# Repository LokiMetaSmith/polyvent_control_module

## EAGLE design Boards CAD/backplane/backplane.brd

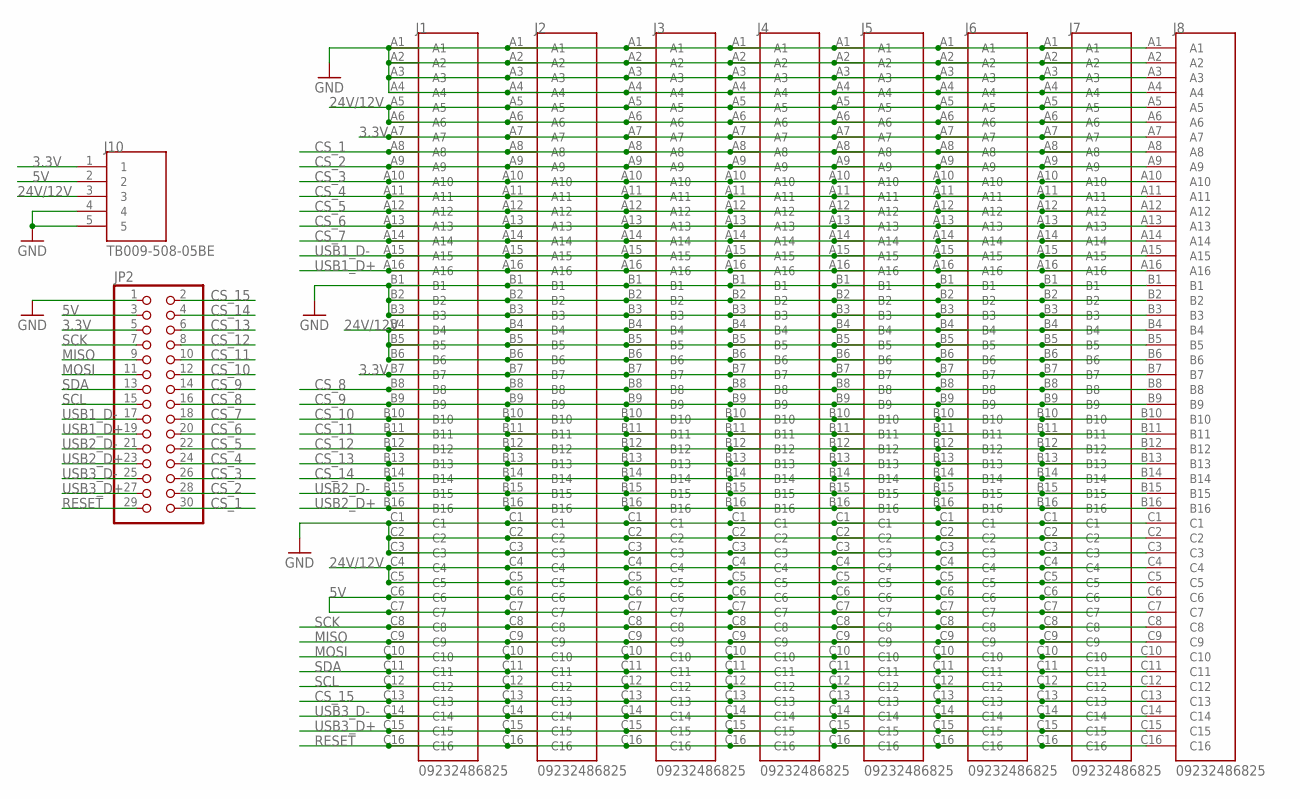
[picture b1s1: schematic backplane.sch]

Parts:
J1, J2, J3, J4, J5, J6, J7, J8: 09232486825; HARTING_09232486825
J10: TB009-508-05BE; CUI_TB009-508-05BE
JP2: PINHD-2X15; 2X15

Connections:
3.3V: J1.A7, J1.B7, J2.A7, J2.B7, J3.A7, J3.B7, J4.A7, J4.B7, J5.A7, J5.B7, J6.A7, J6.B7, J7.A7, J7.B7, J8.A7, J8.B7, J10.1, JP2.5
5V: J1.C6, J1.C7, J2.C6, J2.C7, J3.C6, J3.C7, J4.C6, J4.C7, J5.C6, J5.C7, J6.C6, J6.C7, J7.C6, J7.C7, J8.C6, J8.C7, J10.2, JP2.3
24V/12V: J1.A5, J1.A6, J1.B4, J1.B5, J1.B6, J1.C4, J1.C5, J2.A5, J2.A6, J2.B4, J2.B5, J2.B6, J2.C4, J2.C5, J3.A5, J3.A6, J3.B4, J3.B5, J3.B6, J3.C4, J3.C5, J4.A5, J4.A6, J4.B4, J4.B5, J4.B6, J4.C4, J4.C5, J5.A5, J5.A6, J5.B4, J5.B5, J5.B6, J5.C4, J5.C5, J6.A5, J6.A6, J6.B4, J6.B5, J6.B6, J6.C4, J6.C5, J7.A5, J7.A6, J7.B4, J7.B5, J7.B6, J7.C4, J7.C5, J8.A5, J8.A6, J8.B4, J8.B5, J8.B6, J8.C4, J8.C5, J10.3
CS_1: J1.A8, J2.A8, J3.A8, J4.A8, J5.A8, J6.A8, J7.A8, J8.A8, JP2.30
CS_2: J1.A9, J2.A9, J3.A9, J4.A9, J5.A9, J6.A9, J7.A9, J8.A9, JP2.28
CS_3: J1.A10, J2.A10, J3.A10, J4.A10, J5.A10, J6.A10, J7.A10, J8.A10, JP2.26
CS_4: J1.A11, J2.A11, J3.A11, J4.A11, J5.A11, J6.A11, J7.A11, J8.A11, JP2.24
CS_5: J1.A12, J2.A12, J3.A12, J4.A12, J5.A12, J6.A12, J7.A12, J8.A12, JP2.22
CS_6: J1.A13, J2.A13, J3.A13, J4.A13, J5.A13, J6.A13, J7.A13, J8.A13, JP2.20
CS_7: J1.A14, J2.A14, J3.A14, J4.A14, J5.A14, J6.A14, J7.A14, J8.A14, JP2.18
CS_8: J1.B8, J2.B8, J3.B8, J4.B8, J5.B8, J6.B8, J7.B8, J8.B8, JP2.16
CS_9: J1.B9, J2.B9, J3.B9, J4.B9, J5.B9, J6.B9, J7.B9, J8.B9, JP2.14
CS_10: J1.B10, J2.B10, J3.B10, J4.B10, J5.B10, J6.B10, J7.B10, J8.B10, JP2.12
CS_11: J1.B11, J2.B11, J3.B11, J4.B11, J5.B11, J6.B11, J7.B11, J8.B11, JP2.10
CS_12: J1.B12, J2.B12, J3.B12, J4.B12, J5.B12, J6.B12, J7.B12, J8.B12, JP2.8
CS_13: J1.B13, J2.B13, J3.B13, J4.B13, J5.B13, J6.B13, J7.B13, J8.B13, JP2.6
CS_14: J1.B14, J2.B14, J3.B14, J4.B14, J5.B14, J6.B14, J7.B14, J8.B14, JP2.4
CS_15: J1.C13, J2.C13, J3.C13, J4.C13, J5.C13, J6.C13, J7.C13, J8.C13, JP2.2
GND: J1.A1, J1.A2, J1.A3, J1.A4, J1.B1, J1.B2, J1.B3, J1.C1, J1.C2, J1.C3, J2.A1, J2.A2, J2.A3, J2.A4, J2.B1, J2.B2, J2.B3, J2.C1, J2.C2, J2.C3, J3.A1, J3.A2, J3.A3, J3.A4, J3.B1, J3.B2, J3.B3, J3.C1, J3.C2, J3.C3, J4.A1, J4.A2, J4.A3, J4.A4, J4.B1, J4.B2, J4.B3, J4.C1, J4.C2, J4.C3, J5.A1, J5.A2, J5.A3, J5.A4, J5.B1, J5.B2, J5.B3, J5.C1, J5.C2, J5.C3, J6.A1, J6.A2, J6.A3, J6.A4, J6.B1, J6.B2, J6.B3, J6.C1, J6.C2, J6.C3, J7.A1, J7.A2, J7.A3, J7.A4, J7.B1, J7.B2, J7.B3, J7.C1, J7.C2, J7.C3, J8.A1, J8.A2, J8.A3, J8.A4, J8.B1, J8.B2, J8.B3, J8.C1, J8.C2, J8.C3, J10.4, J10.5, JP2.1
MISO: J1.C9, J2.C9, J3.C9, J4.C9, J5.C9, J6.C9, J7.C9, J8.C9, JP2.9
MOSI: J1.C10, J2.C10, J3.C10, J4.C10, J5.C10, J6.C10, J7.C10, J8.C10, JP2.11
RESET: J1.C16, J2.C16, J3.C16, J4.C16, J5.C16, J6.C16, J7.C16, J8.C16, JP2.29
SCK: J1.C8, J2.C8, J3.C8, J4.C8, J5.C8, J6.C8, J7.C8, J8.C8, JP2.7
SCL: J1.C12, J2.C12, J3.C12, J4.C12, J5.C12, J6.C12, J7.C12, J8.C12, JP2.15
SDA: J1.C11, J2.C11, J3.C11, J4.C11, J5.C11, J6.C11, J7.C11, J8.C11, JP2.13
USB1_D+: J1.A16, J2.A16, J3.A16, J4.A16, J5.A16, J6.A16, J7.A16, J8.A16, JP2.19
USB1_D-: J1.A15, J2.A15, J3.A15, J4.A15, J5.A15, J6.A15, J7.A15, J8.A15, JP2.17
USB2_D+: J1.B16, J2.B16, J3.B16, J4.B16, J5.B16, J6.B16, J7.B16, J8.B16, JP2.23
USB2_D-: J1.B15, J2.B15, J3.B15, J4.B15, J5.B15, J6.B15, J7.B15, J8.B15, JP2.21
USB3_D+: J1.C15, J2.C15, J3.C15, J4.C15, J5.C15, J6.C15, J7.C15, J8.C15, JP2.27
USB3_D-: J1.C14, J2.C14, J3.C14, J4.C14, J5.C14, J6.C14, J7.C14, J8.C14, JP2.25

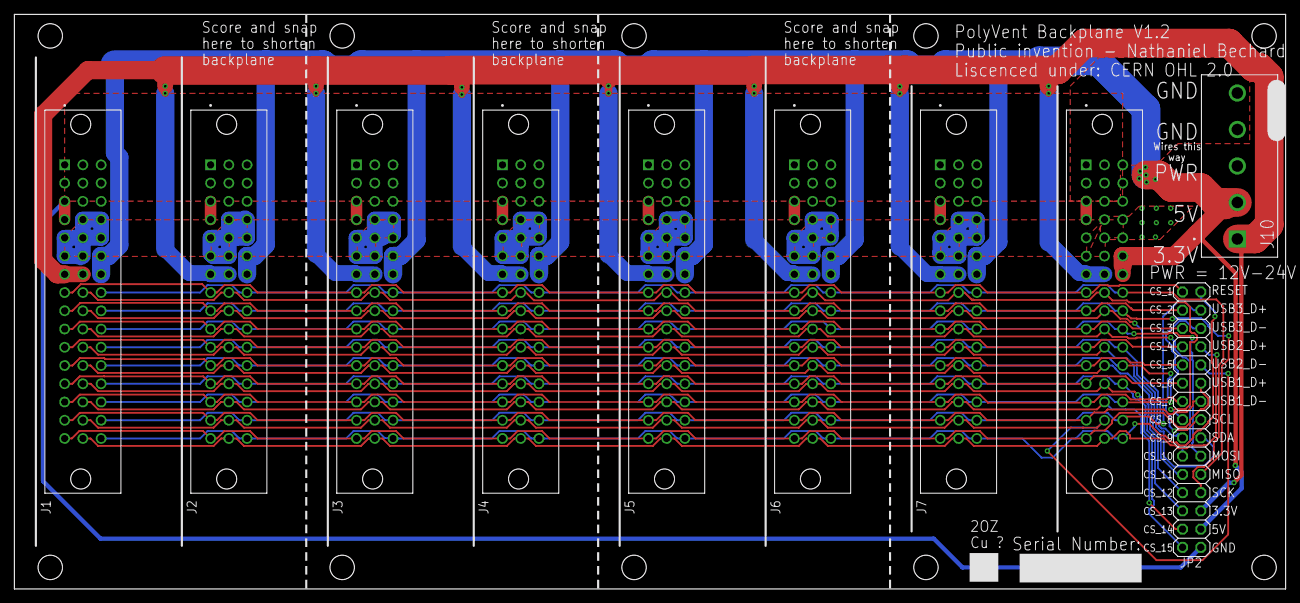
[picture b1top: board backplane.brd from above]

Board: 2 copper layers, 177.0 x 80.0 mm, 10 parts (0 on the bottom side), 31 nets.

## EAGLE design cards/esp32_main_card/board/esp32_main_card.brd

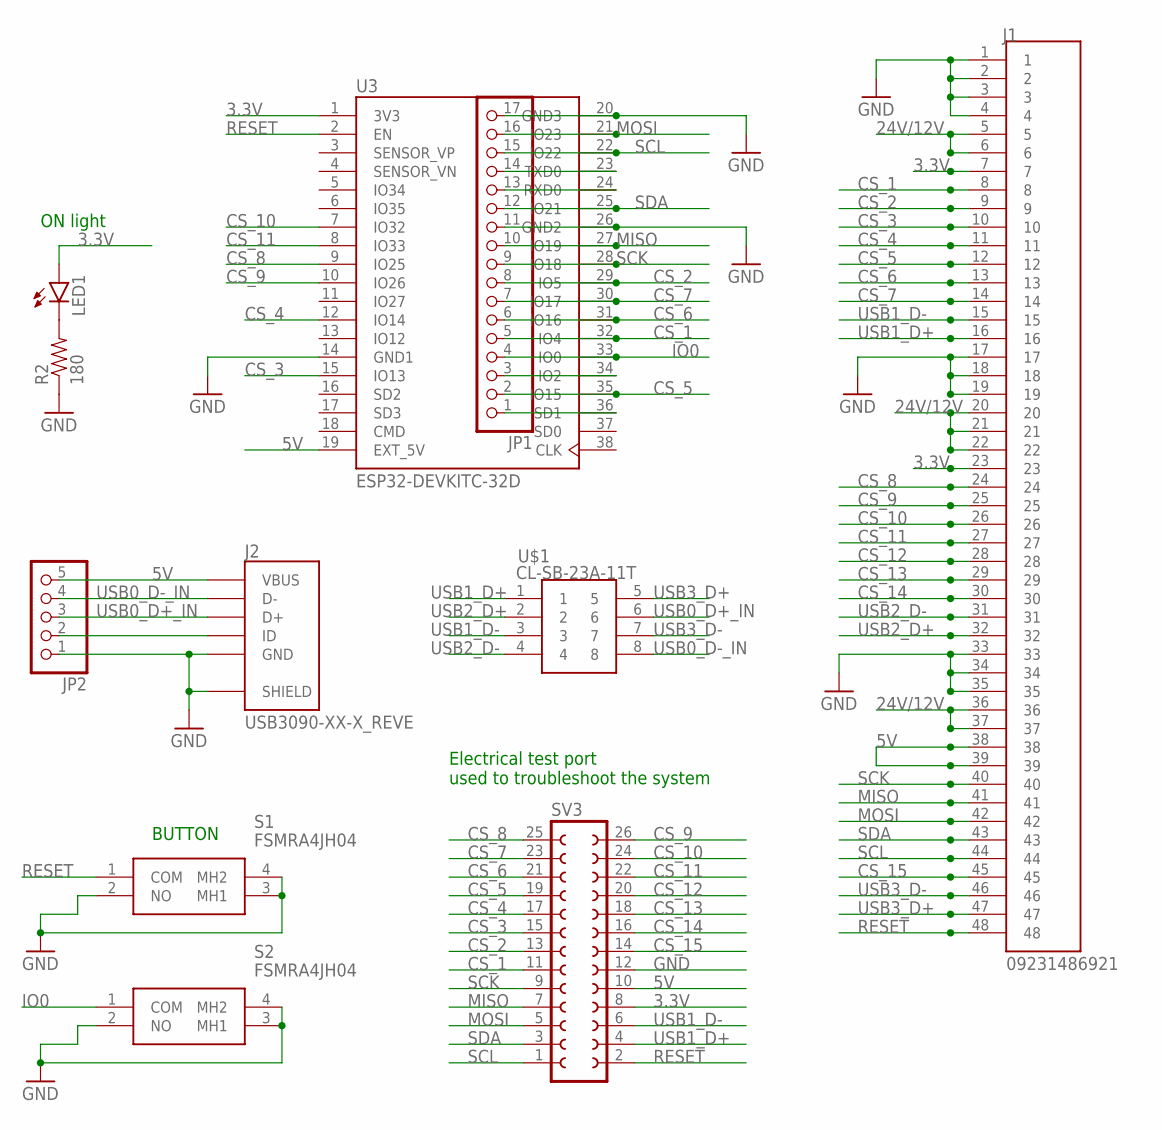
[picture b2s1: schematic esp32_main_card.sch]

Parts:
J1: 09231486921; HARTING_09231486921
J2: USB3090-XX-X_REVE; GCT_USB3090-XX-X_REVE
JP1: PINHD-1X17; 1X17
JP2: PINHD-1X5; 1X05
LED1: LED3MM
R2: 180; 0805
S1, S2: FSMRA4JH04
SV3: FE13-2W
U3: ESP32-DEVKITC-32D; MODULE_ESP32-DEVKITC-32D
U$1: CL-SB-23A-11T

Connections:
3.3V: J1.7, J1.23, LED1.A, SV3.8, U3.1 (3V3)
5V: J1.38, J1.39, J2.1 (VBUS), JP2.5, SV3.10, U3.19 (EXT_5V)
24V/12V: J1.5, J1.6, J1.20, J1.21, J1.22, J1.36, J1.37
CS_1: J1.8, JP1.5, SV3.11, U3.32 (IO4)
CS_2: J1.9, JP1.8, SV3.13, U3.29 (IO5)
CS_3: J1.10, SV3.15, U3.15 (IO13)
CS_4: J1.11, SV3.17, U3.12 (IO14)
CS_5: J1.12, JP1.2, SV3.19, U3.35 (IO15)
CS_6: J1.13, JP1.6, SV3.21, U3.31 (IO16)
CS_7: J1.14, JP1.7, SV3.23, U3.30 (IO17)
CS_8: J1.24, SV3.25, U3.9 (IO25)
CS_9: J1.25, SV3.26, U3.10 (IO26)
CS_10: J1.26, SV3.24, U3.7 (IO32)
CS_11: J1.27, SV3.22, U3.8 (IO33)
CS_12: J1.28, SV3.20
CS_13: J1.29, SV3.18
CS_14: J1.30, SV3.16
CS_15: J1.45, SV3.14
GND: J1.1, J1.2, J1.3, J1.4, J1.17, J1.18, J1.19, J1.33, J1.34, J1.35, J2.5 (GND), J2.6 (SHIELD), J2.7 (SHIELD), J2.8 (SHIELD), J2.9 (SHIELD), JP1.11, JP2.1, R2.1, S1.2 (NO), S1.3 (MH1), S1.4 (MH2), S2.2 (NO), S2.3 (MH1), S2.4 (MH2), SV3.12, U3.14 (GND1), U3.26 (GND2)
IO0: JP1.4, S2.1 (COM), U3.33 (IO0)
MISO: J1.41, JP1.10, SV3.7, U3.27 (IO19)
MOSI: J1.42, JP1.16, SV3.5, U3.21 (IO23)
unnamed: J2.4 (ID), JP2.2
unnamed: JP1.17, U3.20 (GND3)
unnamed: JP1.14, U3.23 (TXD0)
unnamed: JP1.13, U3.24 (RXD0)
unnamed: JP1.3, U3.34 (IO2)
unnamed: JP1.1, U3.36 (SD1)
unnamed: LED1.K (C), R2.2
RESET: J1.48, S1.1 (COM), SV3.2, U3.2 (EN)
SCK: J1.40, JP1.9, SV3.9, U3.28 (IO18)
SCL: J1.44, JP1.15, SV3.1, U3.22 (IO22)
SDA: J1.43, JP1.12, SV3.3, U3.25 (IO21)
USB0_D+_IN: J2.3 (D+), JP2.3, U$1.6
USB0_D-_IN: J2.2 (D-), JP2.4, U$1.8
USB1_D+: J1.16, SV3.4, U$1.1
USB1_D-: J1.15, SV3.6, U$1.3
USB2_D+: J1.32, U$1.2
USB2_D-: J1.31, U$1.4
USB3_D+: J1.47, U$1.5
USB3_D-: J1.46, U$1.7

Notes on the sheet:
Electrical test port used to troubleshoot the system
BUTTON
ON light

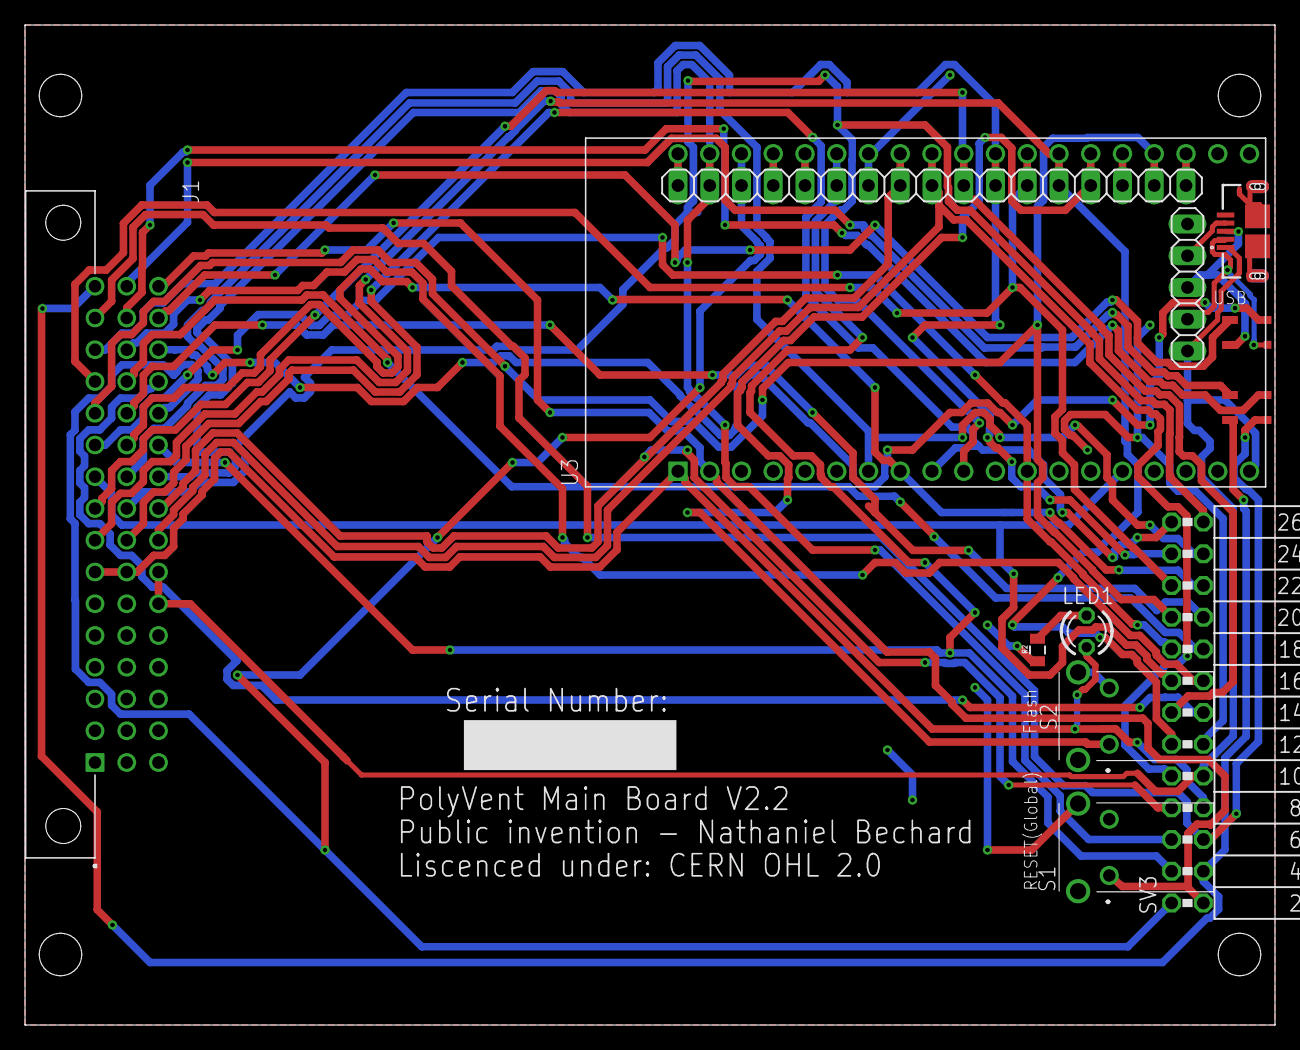
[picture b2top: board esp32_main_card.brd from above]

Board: 2 copper layers, 100.0 x 80.0 mm, 11 parts (0 on the bottom side), 41 nets.

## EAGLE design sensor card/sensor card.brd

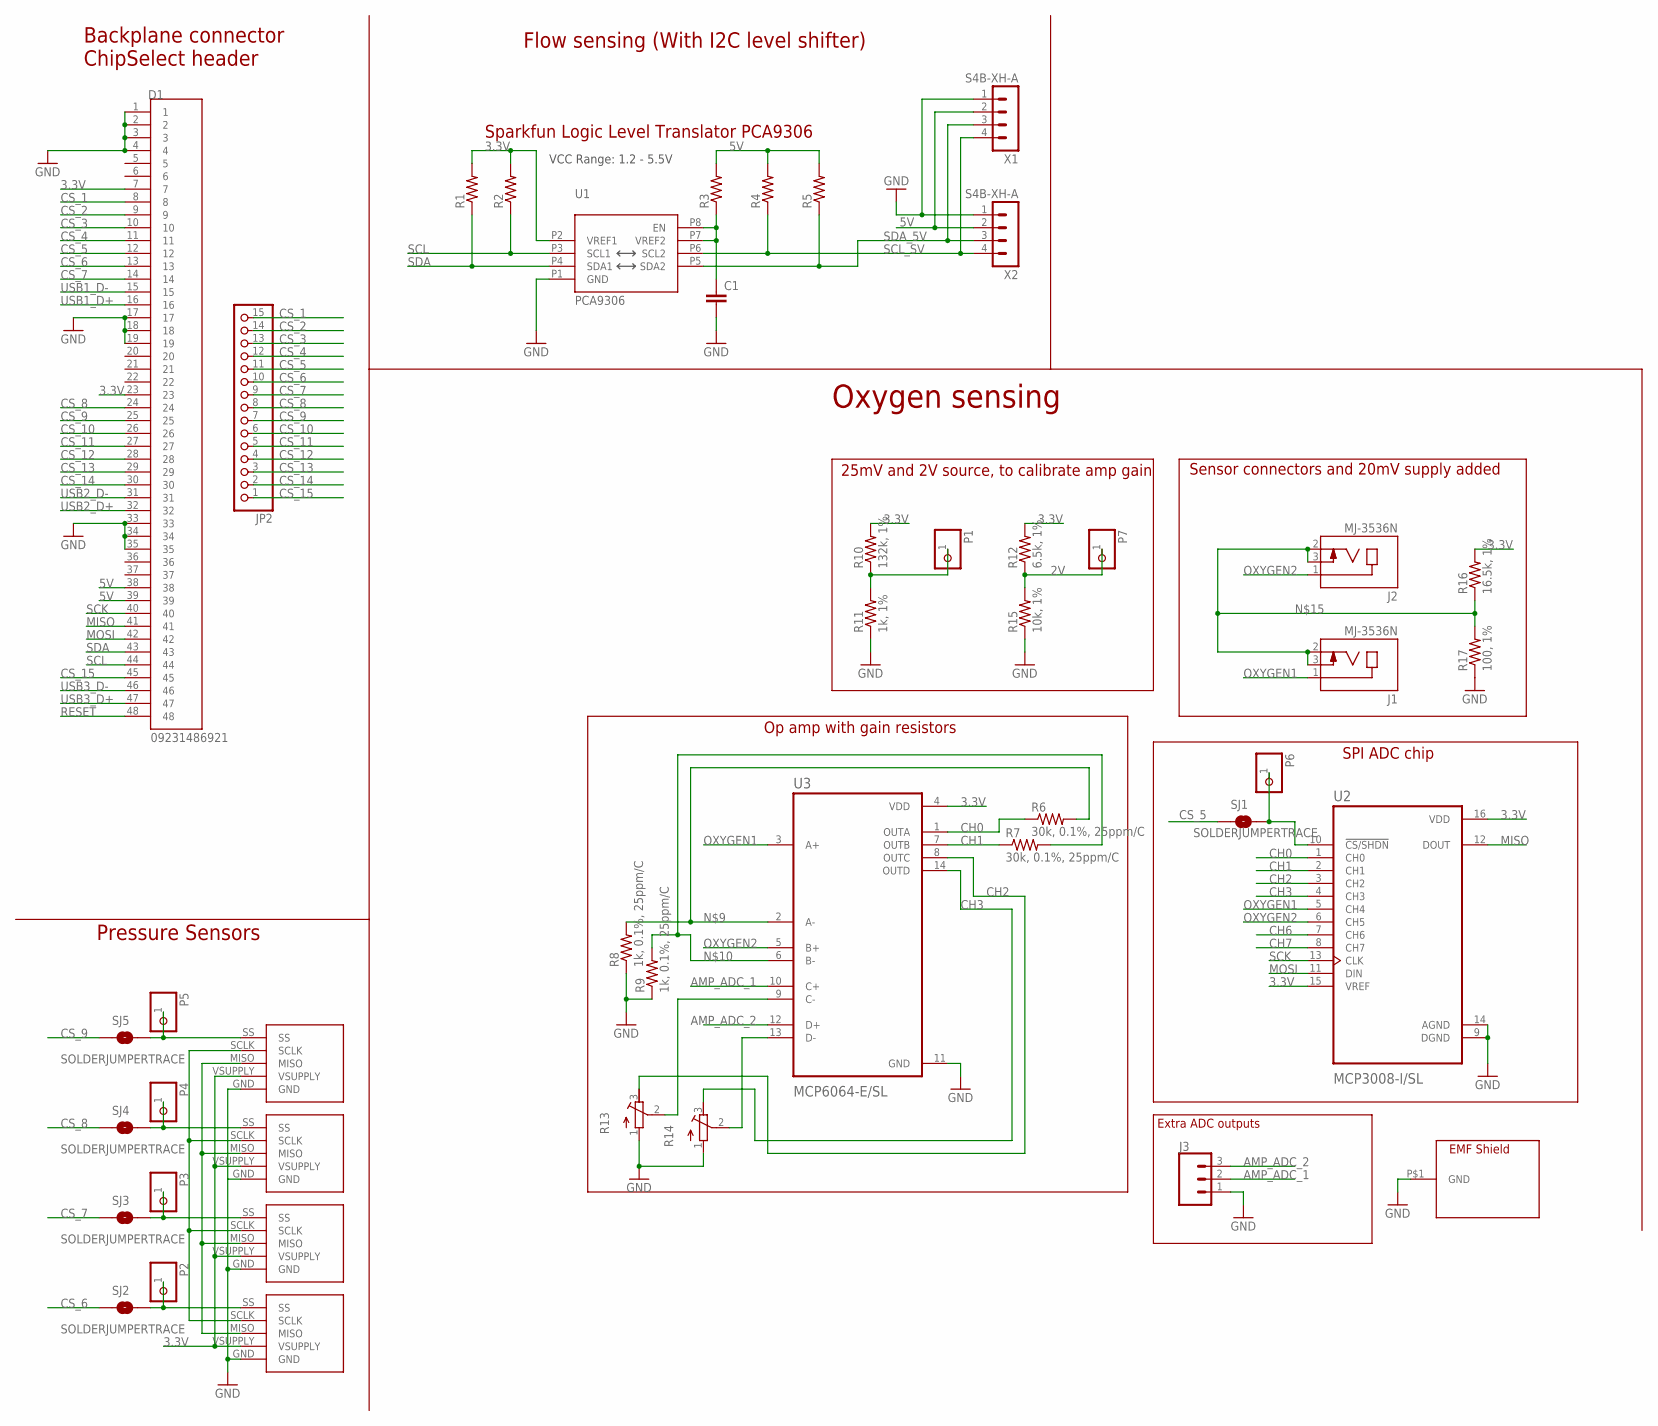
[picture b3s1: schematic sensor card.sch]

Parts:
C1: 100pF; 0805
D1: 09231486921; HARTING_09231486921
J1, J2: MJ-3536N; CUI_MJ-3536N
J3: CONN_03; 1X03
JP2: PINHD-1X15; 1X15
P1, P2, P3, P4, P5, P6, P7: PINHD-1X1; 1X01
R1, R2, R4, R5: 2.2k; 0805
R3: 200K; 0805
R6, R7: 30k, 0.1%, 25ppm/C; 0805
R8, R9: 1k, 0.1%, 25ppm/C; 0805
R10: 132k, 1%; 0805
R11: 1k, 1%; 0805
R12: 6.5k, 1%; 0805
R13, R14: R-TRIMM3214W; RTRIM3214W
R15: 10k, 1%; 0805
R16: 16.5k, 1%; 0805
R17: 100, 1%; 0805
SJ1, SJ2, SJ3, SJ4, SJ5: SOLDERJUMPERTRACE; SJ_2S-TRACE
U1: PCA9306; VSSOP_8PIN
U2: MCP3008-I/SL; SOIC127P600X175-16N
U3: MCP6064-E/SL; SOIC127P600X175-14N
U$1, U$3, U$4, U$5: SCCDRRV100MDSA3SSCDRRV100MDSA3; DIP1270W53P254L1303H508Q8B
U$2: EMI_SHIELD; 3671250
X1, X2: S4B-XH-A

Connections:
2V: P7.1, R12.1, R15.2
3.3V: D1.7, D1.23, R1.2, R2.2, R10.2, R12.2, R16.2, U1.P2 (VREF1), U2.15 (VREF), U2.16 (VDD), U3.4 (VDD), U$1.VSUPPLY, U$3.VSUPPLY, U$4.VSUPPLY, U$5.VSUPPLY
5V: D1.38, D1.39, R3.2, R4.2, R5.2, X1.2, X2.2
50MILIVOLT: P1.1, R10.1, R11.2
AMP_ADC_1: J3.2, U3.10 (C+)
AMP_ADC_2: J3.3, U3.12 (D+)
CH0: R6.1, U2.1 (CH0), U3.1 (OUTA)
CH1: R7.1, U2.2 (CH1), U3.7 (OUTB)
CH2: R13.3 (E), U2.3 (CH2), U3.8 (OUTC)
CH3: R14.3 (E), U2.4 (CH3), U3.14 (OUTD)
CH6: U2.7 (CH6)
CH7: U2.8 (CH7)
CS_1: D1.8, JP2.15
CS_2: D1.9, JP2.14
CS_3: D1.10, JP2.13
CS_4: D1.11, JP2.12
CS_5: D1.12, JP2.11, SJ1.1
CS_6: D1.13, JP2.10, SJ2.1
CS_7: D1.14, JP2.9, SJ3.1
CS_8: D1.24, JP2.8, SJ4.1
CS_9: D1.25, JP2.7, SJ5.1
CS_10: D1.26, JP2.6
CS_11: D1.27, JP2.5
CS_12: D1.28, JP2.4
CS_13: D1.29, JP2.3
CS_14: D1.30, JP2.2
CS_15: D1.45, JP2.1
GND: C1.2, D1.1, D1.2, D1.3, D1.4, D1.17, D1.18, D1.19, D1.33, D1.34, D1.35, J3.1, R8.1, R9.1, R11.1, R13.1 (A), R14.1 (A), R15.1, R17.1, U1.P1 (GND), U2.9 (DGND), U2.14 (AGND), U3.11 (GND), U$1.GND, U$2.P$1, U$3.GND, U$4.GND, U$5.GND, X1.1, X2.1
MISO: D1.41, U2.12 (DOUT), U$1.MISO, U$3.MISO, U$4.MISO, U$5.MISO
MOSI: D1.42, U2.11 (DIN)
unnamed: R14.2 (S), U3.13 (D-)
unnamed: P6.1, SJ1.2, U2.10 (!CS/SHDN)
unnamed: P2.1, SJ2.2, U$5.SS
unnamed: R13.2 (S), U3.9 (C-)
unnamed: R6.2, R8.2, U3.2 (A-)
unnamed: R7.2, R9.2, U3.6 (B-)
unnamed: P4.1, SJ4.2, U$3.SS
unnamed: P5.1, SJ5.2, U$1.SS
unnamed: J1.2, J1.3, J2.2, J2.3, R16.1, R17.2
unnamed: P3.1, SJ3.2, U$4.SS
OXYGEN1: J1.1, U2.5 (CH4), U3.3 (A+)
OXYGEN2: J2.1, U2.6 (CH5), U3.5 (B+)
RESET: D1.48
SCK: D1.40, U2.13 (CLK), U$1.SCLK, U$3.SCLK, U$4.SCLK, U$5.SCLK
SCL: D1.44, R2.1, U1.P3 (SCL1)
SCL_SV: R4.1, U1.P6 (SCL2), X1.4, X2.4
SDA: D1.43, R1.1, U1.P4 (SDA1)
SDA_5V: R5.1, U1.P5 (SDA2), X1.3, X2.3
USB1_D+: D1.16
USB1_D-: D1.15
USB2_D+: D1.32
USB2_D-: D1.31
USB3_D+: D1.47
USB3_D-: D1.46
VREF2_IN: C1.1, R3.1, U1.P7 (VREF2), U1.P8 (EN)

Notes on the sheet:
Sparkfun Logic Level Translator PCA9306
VCC Range: 1.2 - 5.5V
25mV and 2V source, to calibrate amp gain
Pressure Sensors
Backplane connector ChipSelect header
Flow sensing (With I2C level shifter)
Oxygen sensing
Sensor connectors and 20mV supply added
SPI ADC chip
Op amp with gain resistors
Extra ADC outputs

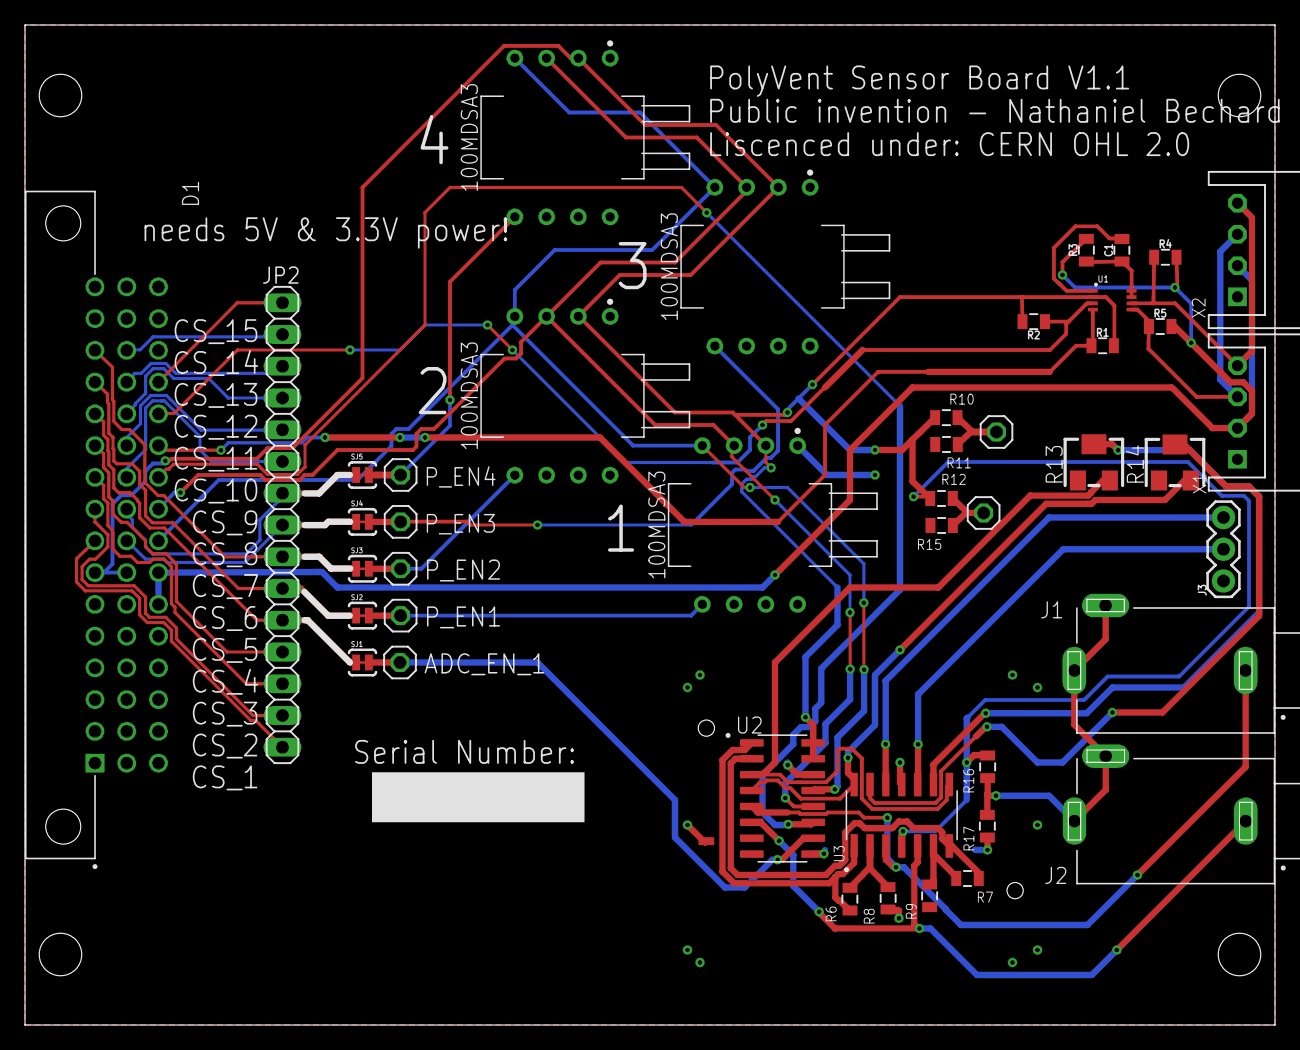
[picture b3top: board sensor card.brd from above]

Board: 2 copper layers, 100.0 x 80.0 mm, 45 parts (0 on the bottom side), 46 nets.

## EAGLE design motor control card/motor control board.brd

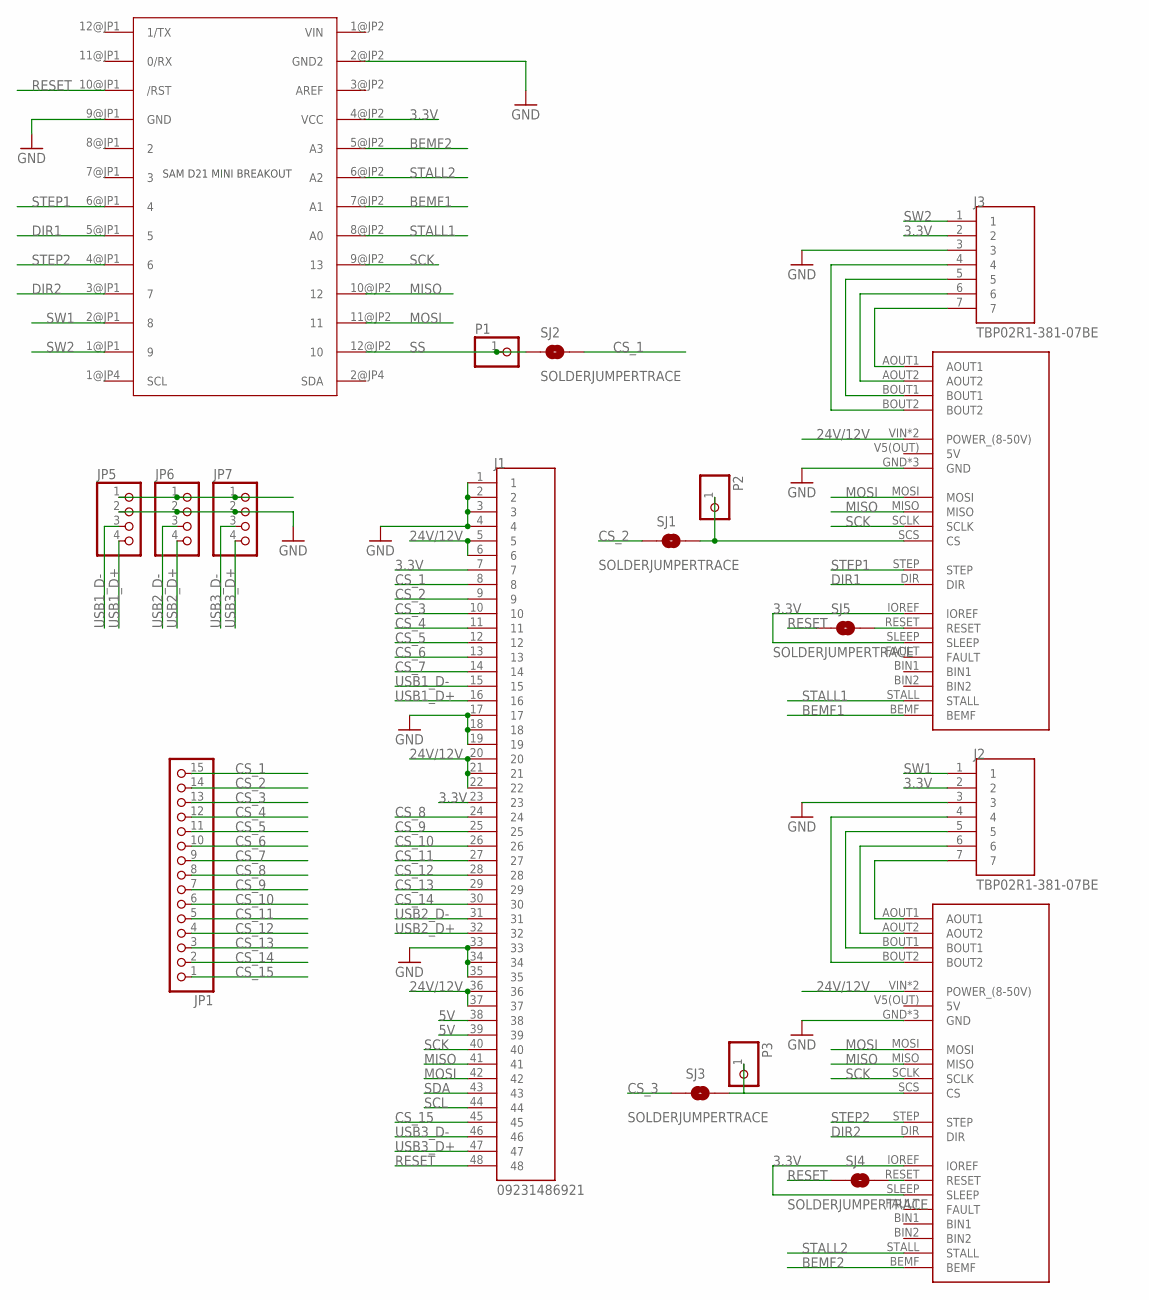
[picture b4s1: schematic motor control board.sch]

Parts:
J1: 09231486921; HARTING_09231486921
J2, J3: TBP02R1-381-07BE; CUI_TBP02R1-381-07BE
JP1: PINHD-1X15; 1X15
JP5, JP6, JP7: PINHD-1X4; 1X04
P1, P2, P3: PINHD-1X1; 1X01
SJ1, SJ2, SJ3, SJ4, SJ5: SOLDERJUMPERTRACE; SJ_2S-TRACE
U$1, U$2: POLOLU_HIGH-POWER_STEPPER_MOTOR_DRIVER_36V4; BREAKOUT_BOARD
U$4: SAM_D21_MINI_BREAKOUT; JP1_SPARKFUN-SAMD21-MINI-BREAKOUT-V10

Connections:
3.3V: J1.7, J1.23, J2.2, J3.2, U$1.IOREF, U$1.SLEEP, U$2.IOREF, U$2.SLEEP, U$4.4@JP2 (VCC)
5V: J1.38, J1.39, JP5.1, JP6.1, JP7.1
24V/12V: J1.5, J1.6, J1.20, J1.21, J1.22, J1.36, J1.37, U$1.VIN (POWER_(8-50V)), U$1.VIN_2 (POWER_(8-50V)), U$2.VIN (POWER_(8-50V)), U$2.VIN_2 (POWER_(8-50V))
AREF: U$4.3@JP2 (AREF)
BEMF1: U$1.BEMF, U$4.7@JP2 (A1)
BEMF2: U$2.BEMF, U$4.5@JP2 (A3)
CS_1: J1.8, JP1.15, SJ2.2
CS_2: J1.9, JP1.14, SJ1.1
CS_3: J1.10, JP1.13, SJ3.1
CS_4: J1.11, JP1.12
CS_5: J1.12, JP1.11
CS_6: J1.13, JP1.10
CS_7: J1.14, JP1.9
CS_8: J1.24, JP1.8
CS_9: J1.25, JP1.7
CS_10: J1.26, JP1.6
CS_11: J1.27, JP1.5
CS_12: J1.28, JP1.4
CS_13: J1.29, JP1.3
CS_14: J1.30, JP1.2
CS_15: J1.45, JP1.1
DIR1: U$1.DIR, U$4.5@JP1 (5)
DIR2: U$2.DIR, U$4.3@JP1 (7)
GND: J1.1, J1.2, J1.3, J1.4, J1.17, J1.18, J1.19, J1.33, J1.34, J1.35, J2.3, J3.3, JP5.2, JP6.2, JP7.2, U$1.GND, U$1.GND_2 (GND), U$1.GND_3 (GND), U$2.GND, U$2.GND_2 (GND), U$2.GND_3 (GND), U$4.9@JP1 (GND)
MISO: J1.41, U$1.MISO, U$2.MISO, U$4.10@JP2 (12)
MOSI: J1.42, U$1.MOSI, U$2.MOSI, U$4.11@JP2 (11)
unnamed: J3.7, U$1.AOUT1
unnamed: J3.6, U$1.AOUT2
unnamed: J3.5, U$1.BOUT1
unnamed: J3.4, U$1.BOUT2
unnamed: SJ4.2, U$2.RESET
unnamed: J2.7, U$2.AOUT1
unnamed: J2.6, U$2.AOUT2
unnamed: J2.5, U$2.BOUT1
unnamed: J2.4, U$2.BOUT2
unnamed: P2.1, SJ1.2, U$1.SCS (CS)
unnamed: SJ5.2, U$1.RESET
unnamed: P3.1, SJ3.2, U$2.SCS (CS)
RESET: J1.48, SJ4.1, SJ5.1, U$4.10@JP1 (/RST)
SCK: J1.40, U$1.SCLK, U$2.SCLK, U$4.9@JP2 (13)
SCL: J1.44
SDA: J1.43
SS: P1.1, SJ2.1, U$4.12@JP2 (10)
STALL1: U$1.STALL, U$4.8@JP2 (A0)
STALL2: U$2.STALL, U$4.6@JP2 (A2)
STEP1: U$1.STEP, U$4.6@JP1 (4)
STEP2: U$2.STEP, U$4.4@JP1 (6)
SW1: J2.1, U$4.2@JP1 (8)
SW2: J3.1, U$4.1@JP1 (9)
USB1_D+: J1.16, JP5.4
USB1_D-: J1.15, JP5.3
USB2_D+: J1.32, JP6.4
USB2_D-: J1.31, JP6.3
USB3_D+: J1.47, JP7.4
USB3_D-: J1.46, JP7.3
VIN: U$4.1@JP2 (VIN)

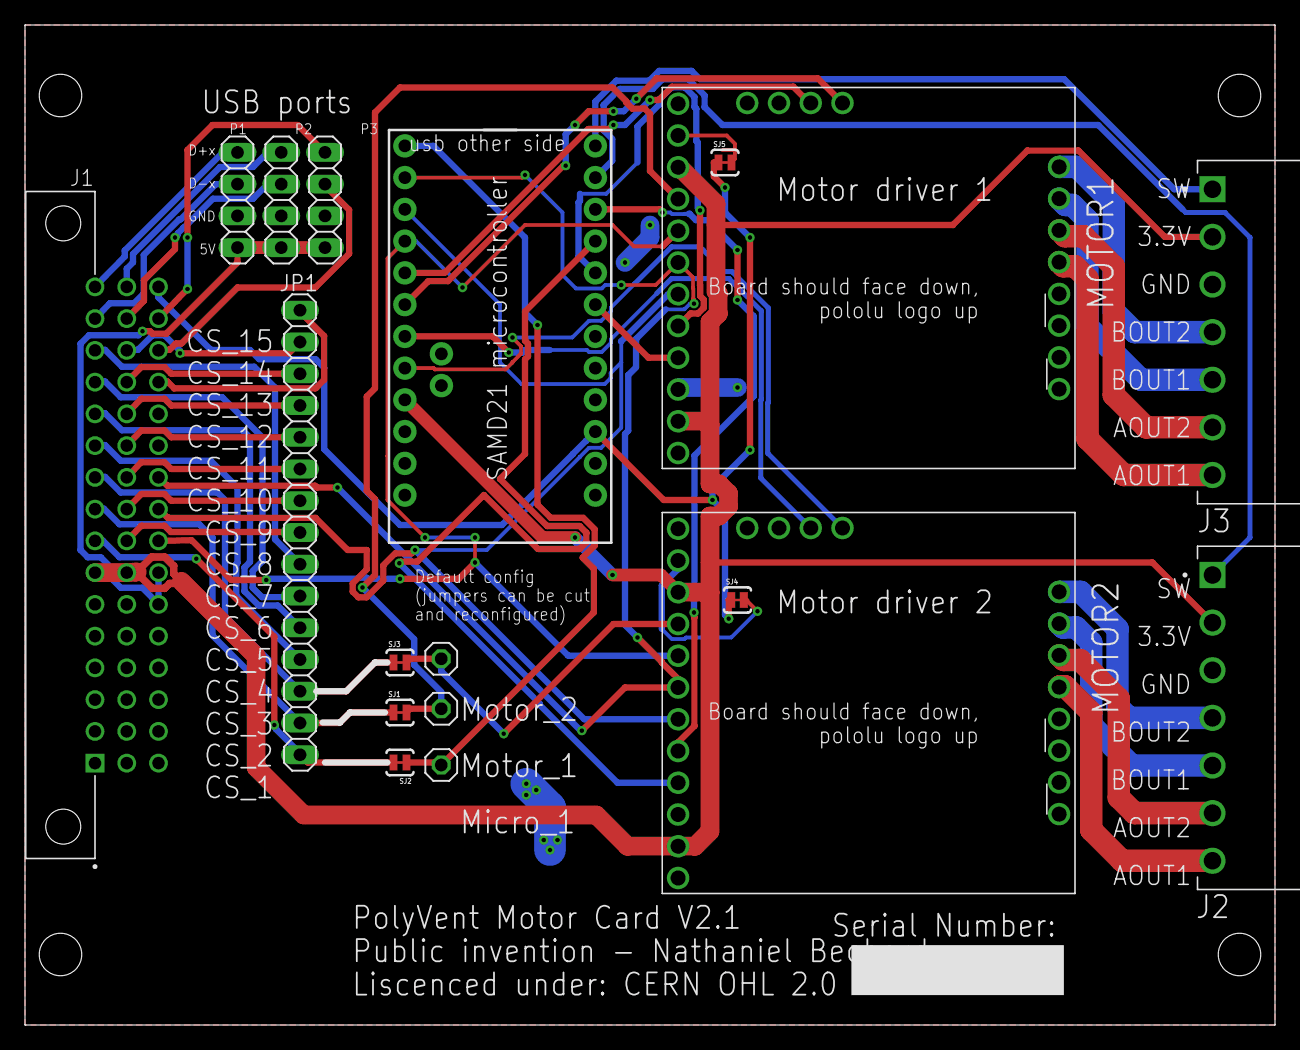
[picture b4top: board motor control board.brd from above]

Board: 2 copper layers, 100.0 x 80.0 mm, 18 parts (0 on the bottom side), 52 nets.

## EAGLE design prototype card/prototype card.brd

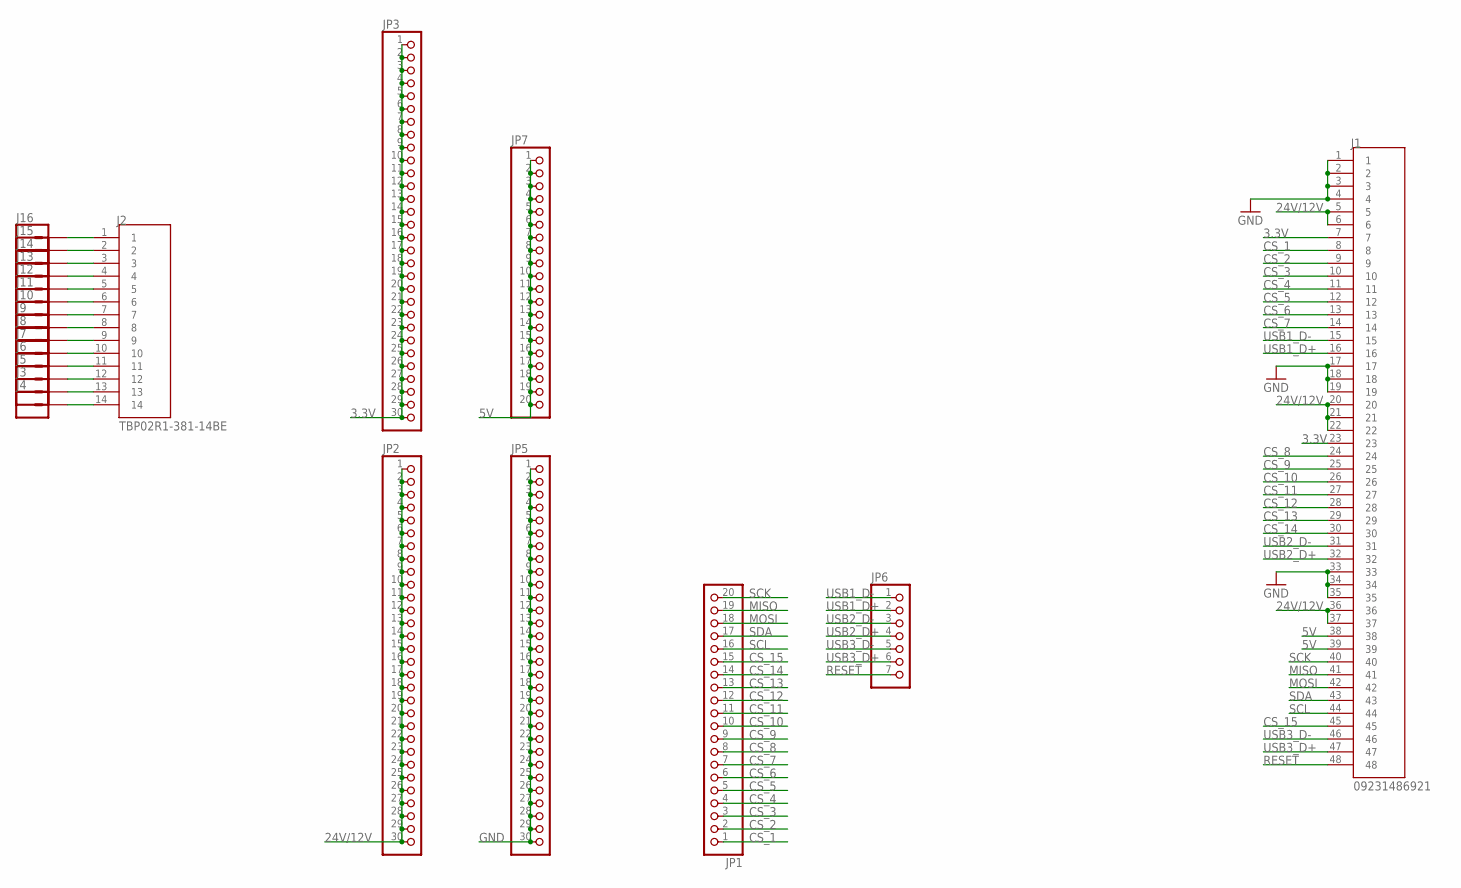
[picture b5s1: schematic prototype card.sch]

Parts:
J1: 09231486921; HARTING_09231486921
J2: TBP02R1-381-14BE; CUI_TBP02R1-381-14BE
J3, J4, J5, J6, J7, J8, J9, J10, J11, J12, J13, J14, J15, J16: CONN_01PTH_LONGPAD; 1X01_LONGPAD
JP1, JP7: PINHD-1X20; 1X20
JP2, JP3, JP5: PINHD-1X30; 1X30
JP6: PINHD-1X7; 1X07

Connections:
3.3V: J1.7, J1.23, JP3.1, JP3.2, JP3.3, JP3.4, JP3.5, JP3.6, JP3.7, JP3.8, JP3.9, JP3.10, JP3.11, JP3.12, JP3.13, JP3.14, JP3.15, JP3.16, JP3.17, JP3.18, JP3.19, JP3.20, JP3.21, JP3.22, JP3.23, JP3.24, JP3.25, JP3.26, JP3.27, JP3.28, JP3.29, JP3.30
5V: J1.38, J1.39, JP7.1, JP7.2, JP7.3, JP7.4, JP7.5, JP7.6, JP7.7, JP7.8, JP7.9, JP7.10, JP7.11, JP7.12, JP7.13, JP7.14, JP7.15, JP7.16, JP7.17, JP7.18, JP7.19, JP7.20
24V/12V: J1.5, J1.6, J1.20, J1.21, J1.22, J1.36, J1.37, JP2.1, JP2.2, JP2.3, JP2.4, JP2.5, JP2.6, JP2.7, JP2.8, JP2.9, JP2.10, JP2.11, JP2.12, JP2.13, JP2.14, JP2.15, JP2.16, JP2.17, JP2.18, JP2.19, JP2.20, JP2.21, JP2.22, JP2.23, JP2.24, JP2.25, JP2.26, JP2.27, JP2.28, JP2.29, JP2.30
CS_1: J1.8, JP1.1
CS_2: J1.9, JP1.2
CS_3: J1.10, JP1.3
CS_4: J1.11, JP1.4
CS_5: J1.12, JP1.5
CS_6: J1.13, JP1.6
CS_7: J1.14, JP1.7
CS_8: J1.24, JP1.8
CS_9: J1.25, JP1.9
CS_10: J1.26, JP1.10
CS_11: J1.27, JP1.11
CS_12: J1.28, JP1.12
CS_13: J1.29, JP1.13
CS_14: J1.30, JP1.14
CS_15: J1.45, JP1.15
GND: J1.1, J1.2, J1.3, J1.4, J1.17, J1.18, J1.19, J1.33, J1.34, J1.35, JP5.1, JP5.2, JP5.3, JP5.4, JP5.5, JP5.6, JP5.7, JP5.8, JP5.9, JP5.10, JP5.11, JP5.12, JP5.13, JP5.14, JP5.15, JP5.16, JP5.17, JP5.18, JP5.19, JP5.20, JP5.21, JP5.22, JP5.23, JP5.24, JP5.25, JP5.26, JP5.27, JP5.28, JP5.29, JP5.30
MISO: J1.41, JP1.19
MOSI: J1.42, JP1.18
unnamed: J2.14, J4.1
unnamed: J2.13, J3.1
unnamed: J2.12, J5.1
unnamed: J2.11, J6.1
unnamed: J2.10, J7.1
unnamed: J2.9, J8.1
unnamed: J2.8, J9.1
unnamed: J2.7, J10.1
unnamed: J2.6, J11.1
unnamed: J2.5, J12.1
unnamed: J2.4, J13.1
unnamed: J2.3, J14.1
unnamed: J2.2, J15.1
unnamed: J2.1, J16.1
RESET: J1.48, JP6.7
SCK: J1.40, JP1.20
SCL: J1.44, JP1.16
SDA: J1.43, JP1.17
USB1_D+: J1.16, JP6.2
USB1_D-: J1.15, JP6.1
USB2_D+: J1.32, JP6.4
USB2_D-: J1.31, JP6.3
USB3_D+: J1.47, JP6.6
USB3_D-: J1.46, JP6.5

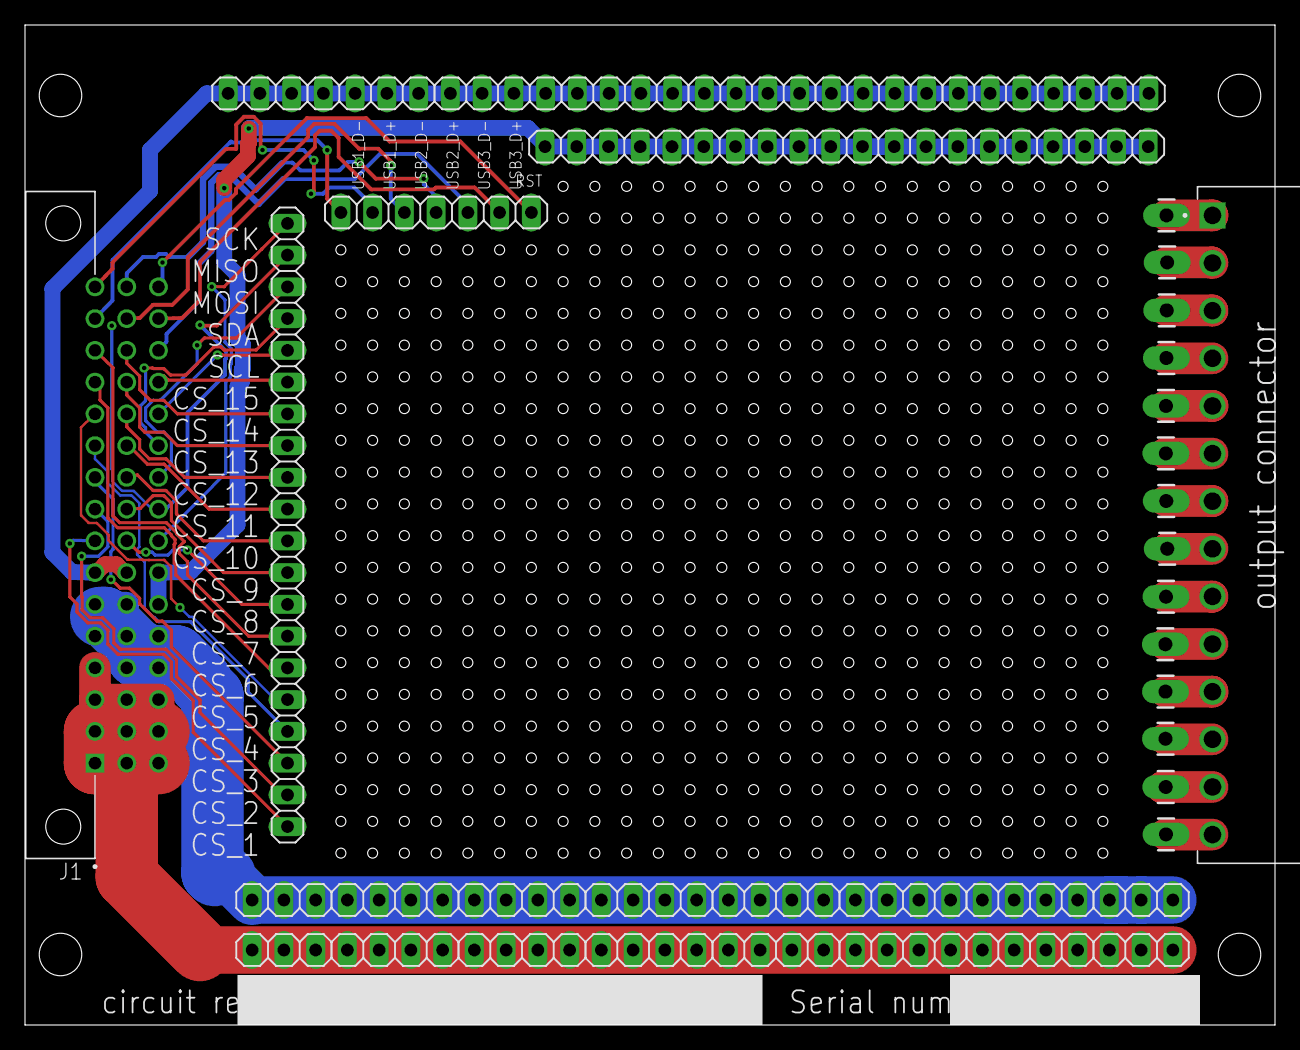
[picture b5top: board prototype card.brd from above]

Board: 2 copper layers, 100.0 x 80.0 mm, 22 parts (0 on the bottom side), 45 nets.

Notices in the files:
Boards CAD/backplane/backplane.brd:
Liscenced under: CERN OHL 2.0
prototype card/prototype card.brd:
PolyVent prototyping board V1.1 - Public Invention -Liscence: CERN OHL V2.0
parts and their libraries:
SparkFun-Passives: Licensing: CC v3.0 Share-Alike You are welcome to use this library for commercial purposes.
SparkFun-Connectors: Licensing: Creative Commons ShareAlike 4.0 International - https://creativecommons.org/licenses/by-sa/4.0
